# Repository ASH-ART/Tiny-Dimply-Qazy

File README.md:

# Tiny Dimply Qazy

A 10.5u 35% keyboard PCB. A tribute to Lazydesigner's Dimple, and tominabox1 and whydobearsexplod's QAZ.

## Status
WIP; awaiting second round of prototyping.

## Layout

<a href="http://www.keyboard-layout-editor.com/#/gists/85e2e431b75c7d8e9e7332ab9f5636bb">Link<a>

## Renders

TODO: Add updated ones after verification

## Specs
* STM32 F072 MCU
* JST SH or Molex EZMate Pico headers
* ESD and overcurrent protection
* Meme cut
* Other stuff like diodes (the cool ones)

## Todo
- [x] Confirm prototype works electronically
- [x] QoL improvements and case fit
- [x] Generic silk with revision number
- [x] Misc. cleanups
- [ ] A la carte gerbers for connector options (JST or EZMate)
- [ ] Use git submodule for parts lib

## Disclaimer

This PCB has been tested to work _electronically_, but requires further prototyping for fit and usability. The members of the PCB development team are not liable if you end up with a non-functional pcb. Order at your own risk. Support will not be provided but pull requests will be reviewed and possibly accepted.

## License

This project is released under the GPL v3 License. Please refer to the LICENCE file.

## Credits

PeppyToad for the layout and pcb help and firmware, ash for the scuffed pcb; lazydesigner, tominabox1, whydobearsexplod and Alas for the inspiration.
Consider BHJ (I hate Bart Harley Jarvis!)

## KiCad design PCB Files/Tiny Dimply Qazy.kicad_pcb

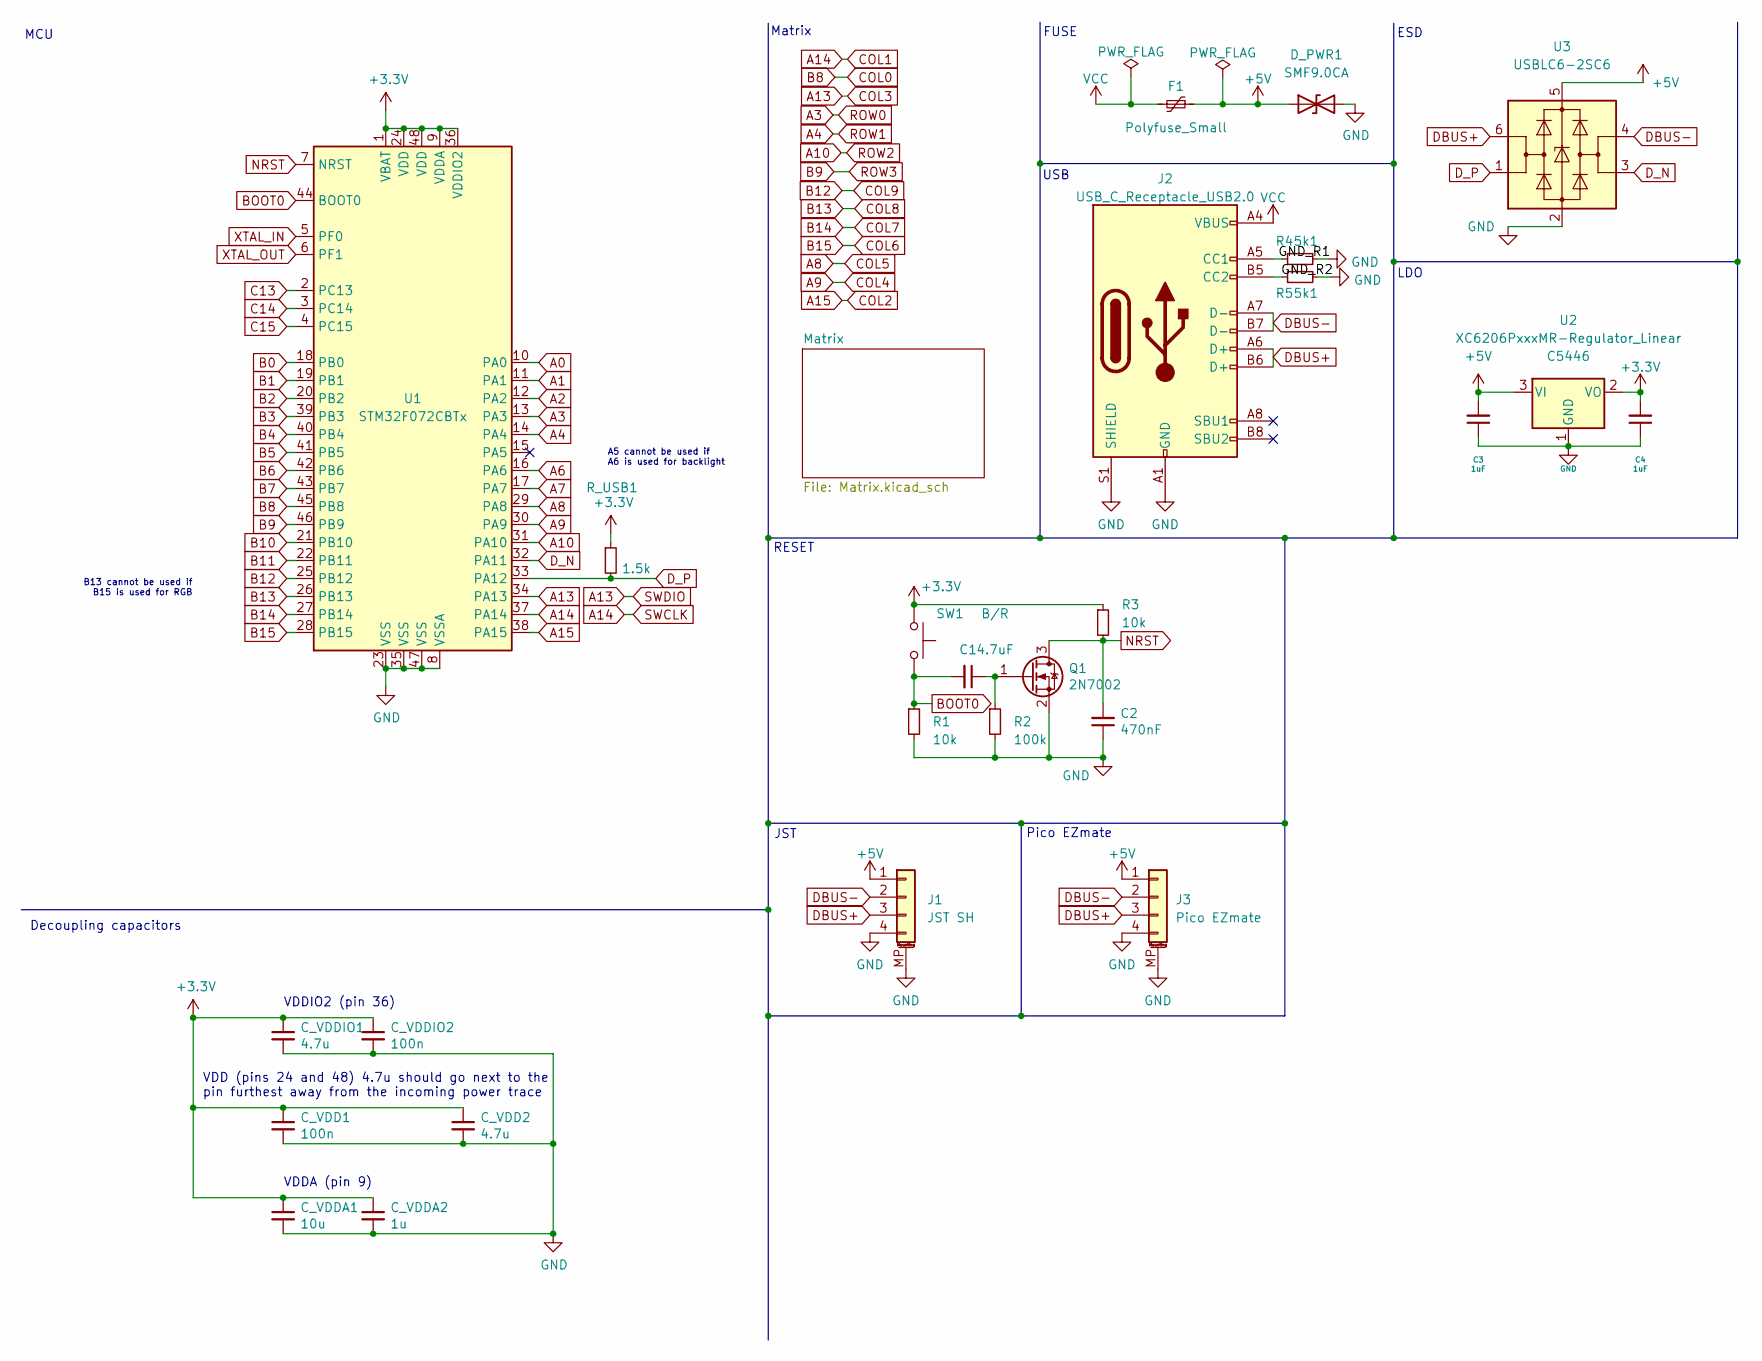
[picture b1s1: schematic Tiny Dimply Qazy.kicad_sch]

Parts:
C1: 4.7uF; C_0402_1005Metric; LCSC C23733
C2: 470nF; C_0402_1005Metric; LCSC C47339
C3, C4: 1uF; C_0402_1005Metric; LCSC C52923
C_VDD1: 100n; C_0603_1608Metric
C_VDD2: 4.7u; C_0603_1608Metric
C_VDDA1: 10u; C_0603_1608Metric
C_VDDA2: 1u; C_0603_1608Metric
C_VDDIO1: 4.7u; C_0603_1608Metric
C_VDDIO2: 100n; C_0603_1608Metric
D_PWR1: SMF9.0CA; D_SOD-123
F1: Polyfuse_Small; Fuse_0603_1608Metric
J1: JST SH; JST_SH_SM04B-SRSS-TB_1x04-1MP_P1.00mm_Horizontal
J2: USB_C_Receptacle_USB2.0; USB_C_Receptacle_HRO_TYPE-C-31-M-12
J3: Pico EZmate; Molex_Pico-EZmate_78171-0004_1x04-1MP_P1.20mm_Vertical
Q1: 2N7002; SOT-23; LCSC C8545
R1, R3: 10k; R_0402_1005Metric; LCSC C25744
R2: 100k; R_0402_1005Metric; LCSC C25741
R4, R5: 5k1; R_0603_1608Metric
R_USB1: 1.5k; R_0603_1608Metric
SW1: B/R; SW_SPST_TL3342; LCSC C318884
U1: STM32F072CBTx; LQFP-48_7x7mm_P0.5mm
U2: XC6206PxxxMR-Regulator_Linear; SOT-23; LCSC C5446
U3: USBLC6-2SC6; SOT-23-6; LCSC C2827654

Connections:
+3V3: C4.2, C_VDD1.1, C_VDD2.1, C_VDDA1.1, C_VDDA2.1, C_VDDIO1.1, C_VDDIO2.1, R3.1, R_USB1.1, SW1.1, U1.1 (VBAT), U1.9 (VDDA), U1.24 (VDD), U1.36 (VDDIO2), U1.48 (VDD), U2.2 (VO); also elsewhere on the board
+5V: C3.2, D_PWR1.1 (A1), F1.1, J1.1, J3.1, U2.3 (VI), U3.5 (VBUS)
/GND_R1: J2.A5 (CC1), R4.1
/GND_R2: J2.B5 (CC2), R5.1
A0: U1.10 (PA0)
A1: U1.11 (PA1)
A2: U1.12 (PA2)
A3: U1.13 (PA3); also elsewhere on the board
A4: U1.14 (PA4); also elsewhere on the board
A6: U1.16 (PA6)
A7: U1.17 (PA7)
A9: U1.30 (PA9); also elsewhere on the board
A10: U1.31 (PA10); also elsewhere on the board
A13: U1.34 (PA13); also elsewhere on the board
A14: U1.37 (PA14); also elsewhere on the board
A15: U1.38 (PA15); also elsewhere on the board
B0: U1.18 (PB0)
B1: U1.19 (PB1)
B2: U1.20 (PB2)
B3: U1.39 (PB3)
B4: U1.40 (PB4)
B5: U1.41 (PB5)
B6: U1.42 (PB6)
B7: U1.43 (PB7)
B8: U1.45 (PB8); also elsewhere on the board
B9: U1.46 (PB9); also elsewhere on the board
B10: U1.21 (PB10)
B11: U1.22 (PB11)
BOOT0: C1.2, R1.1, SW1.2, U1.44 (BOOT0)
C13: U1.2 (PC13)
C14: U1.3 (PC14)
C15: U1.4 (PC15)
DBUS+: J1.3, J2.A6 (D+), J2.B6 (D+), J3.3, U3.6 (I/O1)
DBUS-: J1.2, J2.A7 (D-), J2.B7 (D-), J3.2, U3.4 (I/O2)
D_N: U1.32 (PA11), U3.3 (I/O2)
D_P: R_USB1.2, U1.33 (PA12), U3.1 (I/O1)
GND: C2.1, C3.1, C4.1, C_VDD1.2, C_VDD2.2, C_VDDA1.2, C_VDDA2.2, C_VDDIO1.2, C_VDDIO2.2, D_PWR1.2 (A2), J1.4, J1.MP (MountPin), J2.A1 (GND), J2.A12 (GND), J2.B1 (GND), J2.B12 (GND), J2.S1 (SHIELD), J3.4, J3.MP (MountPin), Q1.2 (S), R1.2, R2.2, R4.2, R5.2, U1.8 (VSSA), U1.23 (VSS), U1.35 (VSS), U1.47 (VSS), U2.1 (GND), U3.2 (GND); also elsewhere on the board
NRST: C2.2, Q1.3 (D), R3.2, U1.7 (NRST)
unnamed: C1.1, Q1.1 (G), R2.1
VCC: F1.2, J2.A4 (VBUS), J2.A9 (VBUS), J2.B4 (VBUS), J2.B9 (VBUS)
XTAL_IN: U1.5 (PF0)
XTAL_OUT: U1.6 (PF1)

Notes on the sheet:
RESET
A5 cannot be used if A6 is used for backlight
JST
Decoupling capacitors
VDDIO2 (pin 36)
LDO
Pico EZmate
Matrix
USB
FUSE
MCU
ESD
B13 cannot be used if B15 is used for RGB
VDDA (pin 9)
VDD (pins 24 and 48) 4.7u should go next to the pin furthest away from the incoming power trace

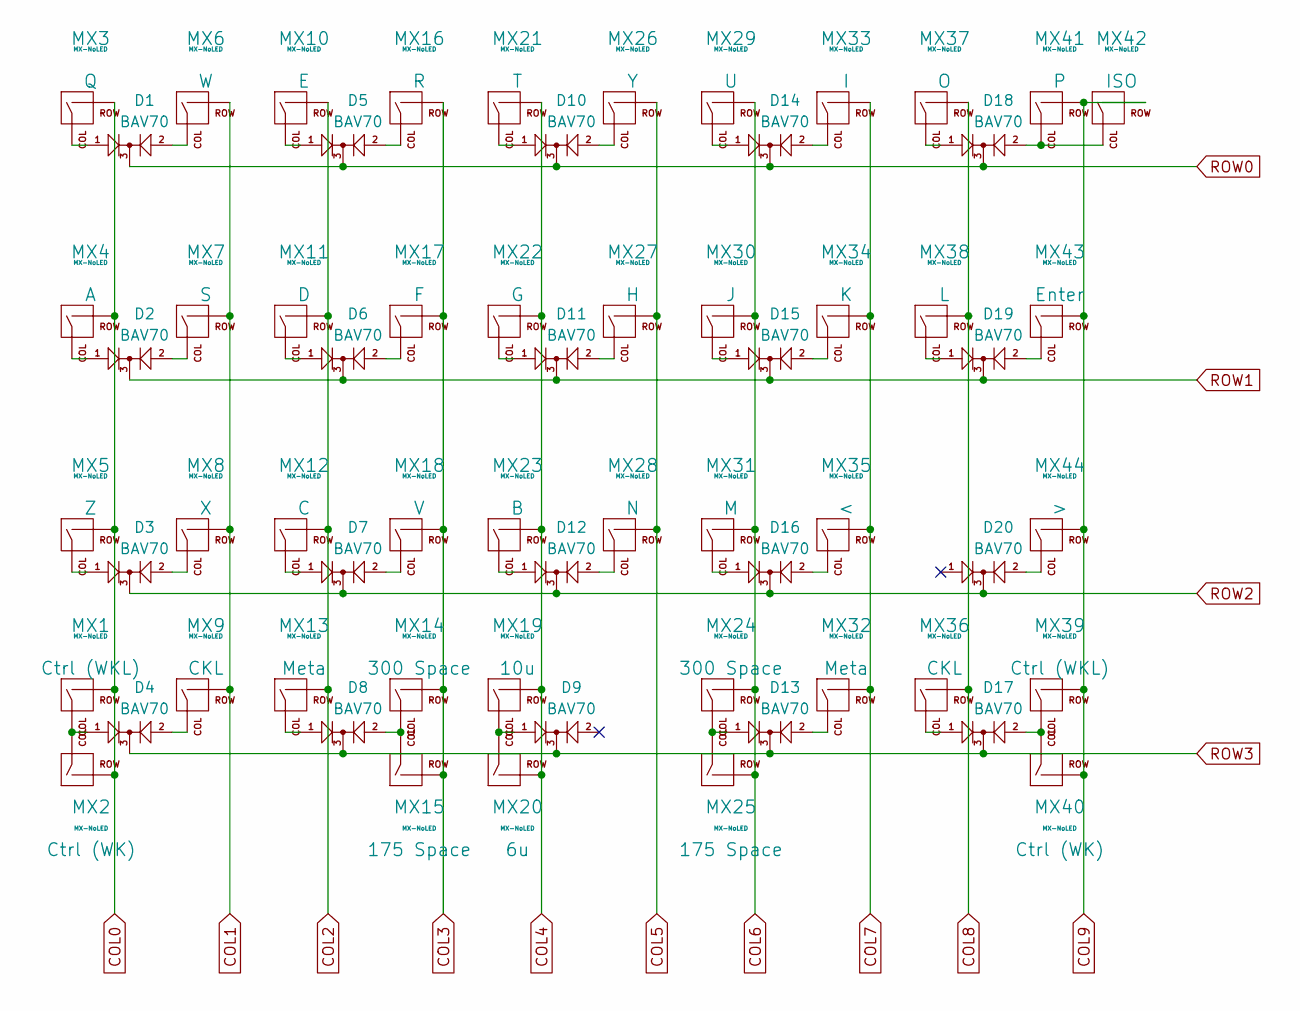
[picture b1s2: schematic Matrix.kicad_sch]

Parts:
D1, D2, D3, D4, D5, D6, D7, D8, D9, D10, D11, D12, D13, D14, D15, D16, D17, D18, D19, D20: BAV70; SOT-23
MX1, MX39, MX41: MX-NoLED; MXOnly-1.5U-NoLED
MX2, MX3, MX6, MX7, MX8, MX10, MX11, MX12, MX16, MX17, MX18, MX21, MX22, MX23, MX26, MX27, MX28, MX29, MX30, MX31, MX33, MX34, MX35, MX37, MX38, MX40: MX-NoLED; MXOnly-1U-NoLED
MX4, MX9, MX13, MX32, MX36, MX43: MX-NoLED; MXOnly-1.25U-NoLED
MX5, MX15, MX25, MX44: MX-NoLED; MXOnly-1.75U-NoLED
MX14, MX24: MX-NoLED; MXOnly-3U-ReversedStabilizers-NoLED
MX19: MX-NoLED; MXOnly-7U-ReversedStabilizers-NoLED
MX20: MX-NoLED; MXOnly-6U-Centered-ReversedStabilizers-NoLED
MX42: MX-NoLED; MXOnly-ISO

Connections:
A3: D1.3 (K), D5.3 (K), D10.3 (K), D14.3 (K), D18.3 (K); also elsewhere on the board
A4: D2.3 (K), D6.3 (K), D11.3 (K), D15.3 (K), D19.3 (K); also elsewhere on the board
A9: MX19.2 (ROW), MX20.2 (ROW), MX21.2 (ROW), MX22.2 (ROW), MX23.2 (ROW); also elsewhere on the board
A10: D3.3 (K), D7.3 (K), D12.3 (K), D16.3 (K), D20.3 (K); also elsewhere on the board
A13: MX14.2 (ROW), MX15.2 (ROW), MX16.2 (ROW), MX17.2 (ROW), MX18.2 (ROW); also elsewhere on the board
A14: MX6.2 (ROW), MX7.2 (ROW), MX8.2 (ROW), MX9.2 (ROW); also elsewhere on the board
A15: MX10.2 (ROW), MX11.2 (ROW), MX12.2 (ROW), MX13.2 (ROW); also elsewhere on the board
B8: MX1.2 (ROW), MX2.2 (ROW), MX3.2 (ROW), MX4.2 (ROW), MX5.2 (ROW); also elsewhere on the board
B9: D4.3 (K), D8.3 (K), D9.3 (K), D13.3 (K), D17.3 (K); also elsewhere on the board
unnamed: D1.1 (A), MX3.1 (COL)
unnamed: D1.2 (A), MX6.1 (COL)
unnamed: D2.1 (A), MX4.1 (COL)
unnamed: D2.2 (A), MX7.1 (COL)
unnamed: D3.1 (A), MX5.1 (COL)
unnamed: D3.2 (A), MX8.1 (COL)
unnamed: D4.1 (A), MX1.1 (COL), MX2.1 (COL)
unnamed: D4.2 (A), MX9.1 (COL)
unnamed: D5.1 (A), MX10.1 (COL)
unnamed: D5.2 (A), MX16.1 (COL)
unnamed: D6.1 (A), MX11.1 (COL)
unnamed: D6.2 (A), MX17.1 (COL)
unnamed: D7.1 (A), MX12.1 (COL)
unnamed: D7.2 (A), MX18.1 (COL)
unnamed: D8.1 (A), MX13.1 (COL)
unnamed: D8.2 (A), MX14.1 (COL), MX15.1 (COL)
unnamed: D9.1 (A), MX19.1 (COL), MX20.1 (COL)
unnamed: D10.1 (A), MX21.1 (COL)
unnamed: D10.2 (A), MX26.1 (COL)
unnamed: D11.1 (A), MX22.1 (COL)
unnamed: D11.2 (A), MX27.1 (COL)
unnamed: D12.1 (A), MX23.1 (COL)
unnamed: D12.2 (A), MX28.1 (COL)
unnamed: D13.1 (A), MX24.1 (COL), MX25.1 (COL)
unnamed: D13.2 (A), MX32.1 (COL)
unnamed: D14.1 (A), MX29.1 (COL)
unnamed: D14.2 (A), MX33.1 (COL)
unnamed: D15.1 (A), MX30.1 (COL)
unnamed: D15.2 (A), MX34.1 (COL)
unnamed: D16.1 (A), MX31.1 (COL)
unnamed: D16.2 (A), MX35.1 (COL)
unnamed: D17.1 (A), MX36.1 (COL)
unnamed: D17.2 (A), MX39.1 (COL), MX40.1 (COL)
unnamed: D18.1 (A), MX37.1 (COL)
unnamed: D18.2 (A), MX41.1 (COL), MX42.1 (COL)
unnamed: D19.1 (A), MX38.1 (COL)
unnamed: D19.2 (A), MX43.1 (COL)
unnamed: D20.2 (A), MX44.1 (COL)

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
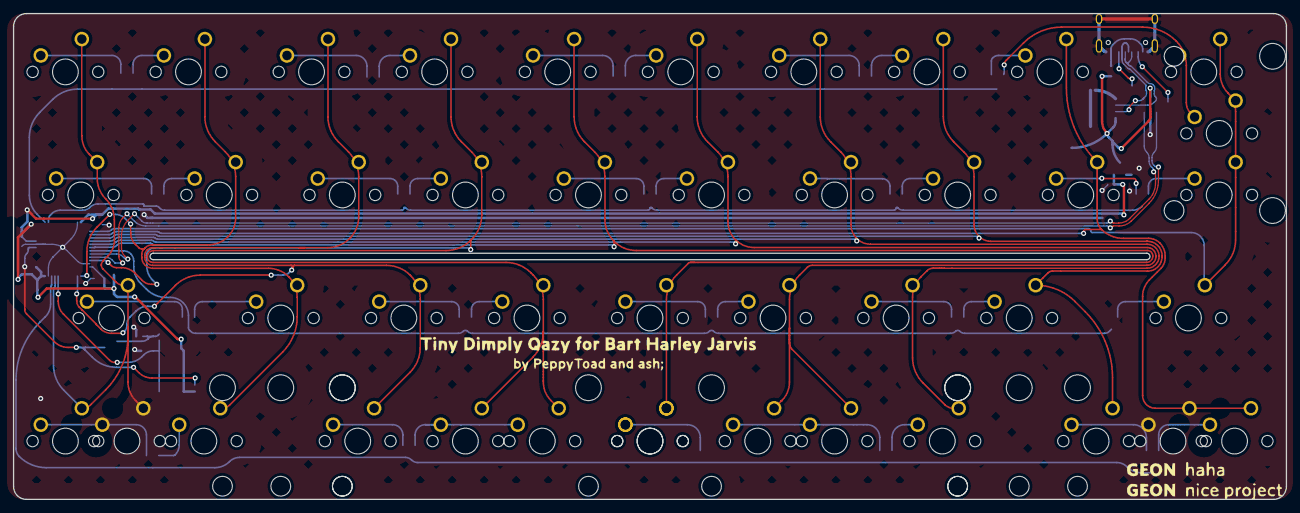
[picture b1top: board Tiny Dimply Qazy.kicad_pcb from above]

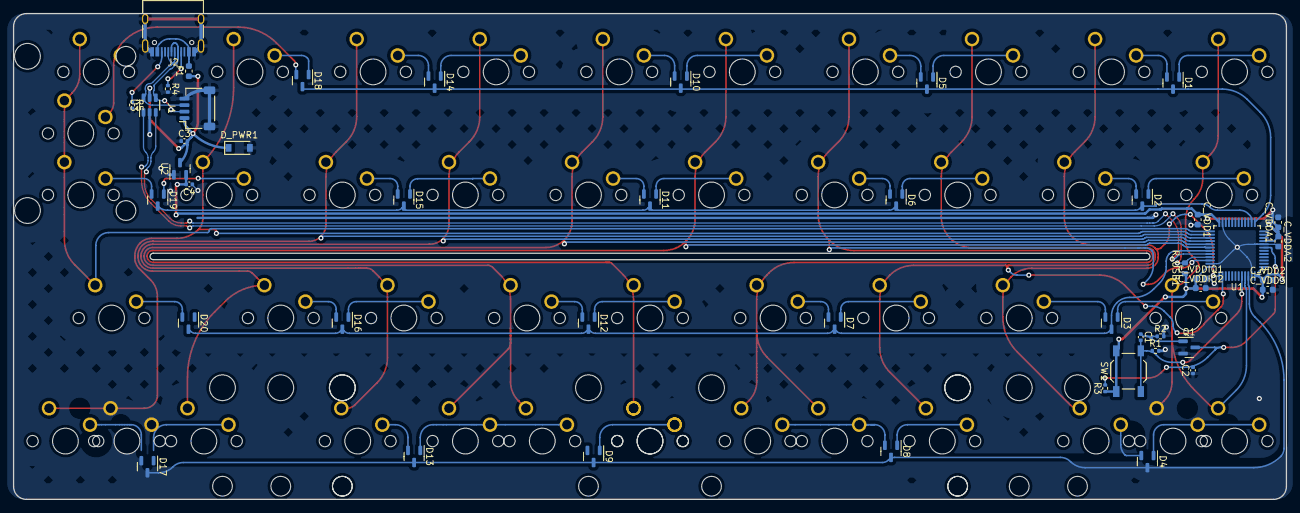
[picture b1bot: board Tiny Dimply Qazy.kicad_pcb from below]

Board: 2 copper layers, 197.0 x 75.2 mm, 91 parts (46 on the bottom side), 65 nets.

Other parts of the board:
C_VDD3: 4.7u; C_0603_1608Metric
Geon: LOGO

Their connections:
+3V3: C_VDD3.1; also elsewhere on the board
GND: C_VDD3.2; also elsewhere on the board

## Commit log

2023-01-02 Initial Commit (adding export files)
2023-01-02 Initial Commit (adding readme and PCB files)
2023-01-02 Rename README.md.txt to README.md
2023-01-02 Delete PCB Files/RP2040_minimal.pretty directory
    The PCB uses an STM MCU and therefore doesn't need the RP2040 library. This is to reduce bloat in the repo
2023-01-02 Delete MCU_RaspberryPi_RP2040.lib
    Same as previous commit (footprint not needed)
2023-01-05 Set gitattributes to LF default line endings
2023-01-05 Set line endings to LF
2023-01-05 Add prototype production changes
    * R4, R5 to 0603 (as requested during prototype PCBA)
    * Replace C_VDD2 with C_VDD3
    * Add missing ground connections for R1, R2
    * Move silk texts to the back
    * Centered big silk text
    * Add Molex EZMate Pico 4-pin header close to the JST SH header
2023-01-05 Change MX32 to 1.25U in the schematic
    No real changes to production files
2023-01-05 Rename Exports/Production files/ -> Exports/jlcpcb/
2023-01-05 We wrote the readme.md with memes
2023-01-05 Added disclaimer to cover our asses
2023-01-05 Add todo section in README.md
2023-01-05 Cleanup the schematics and add a library for smaller bav70s
2023-01-13 Fix outline and bottom row switch positions c/o @ASH-ART
2023-07-12 Update dump
    - Fix bottom row layout
    - Add copium to dubba 1.75u shift using 1.5u and 1.25u
    - Uglify @ASH-ART's routing
    - Generate gerbers as recommended by JLC
    - Add a logotype and revision number
2023-07-12 Fix silk doodoo
2023-07-15 Add o-ring cutouts
2023-07-15 Fix cut-off silk
2023-07-30 Update silks
